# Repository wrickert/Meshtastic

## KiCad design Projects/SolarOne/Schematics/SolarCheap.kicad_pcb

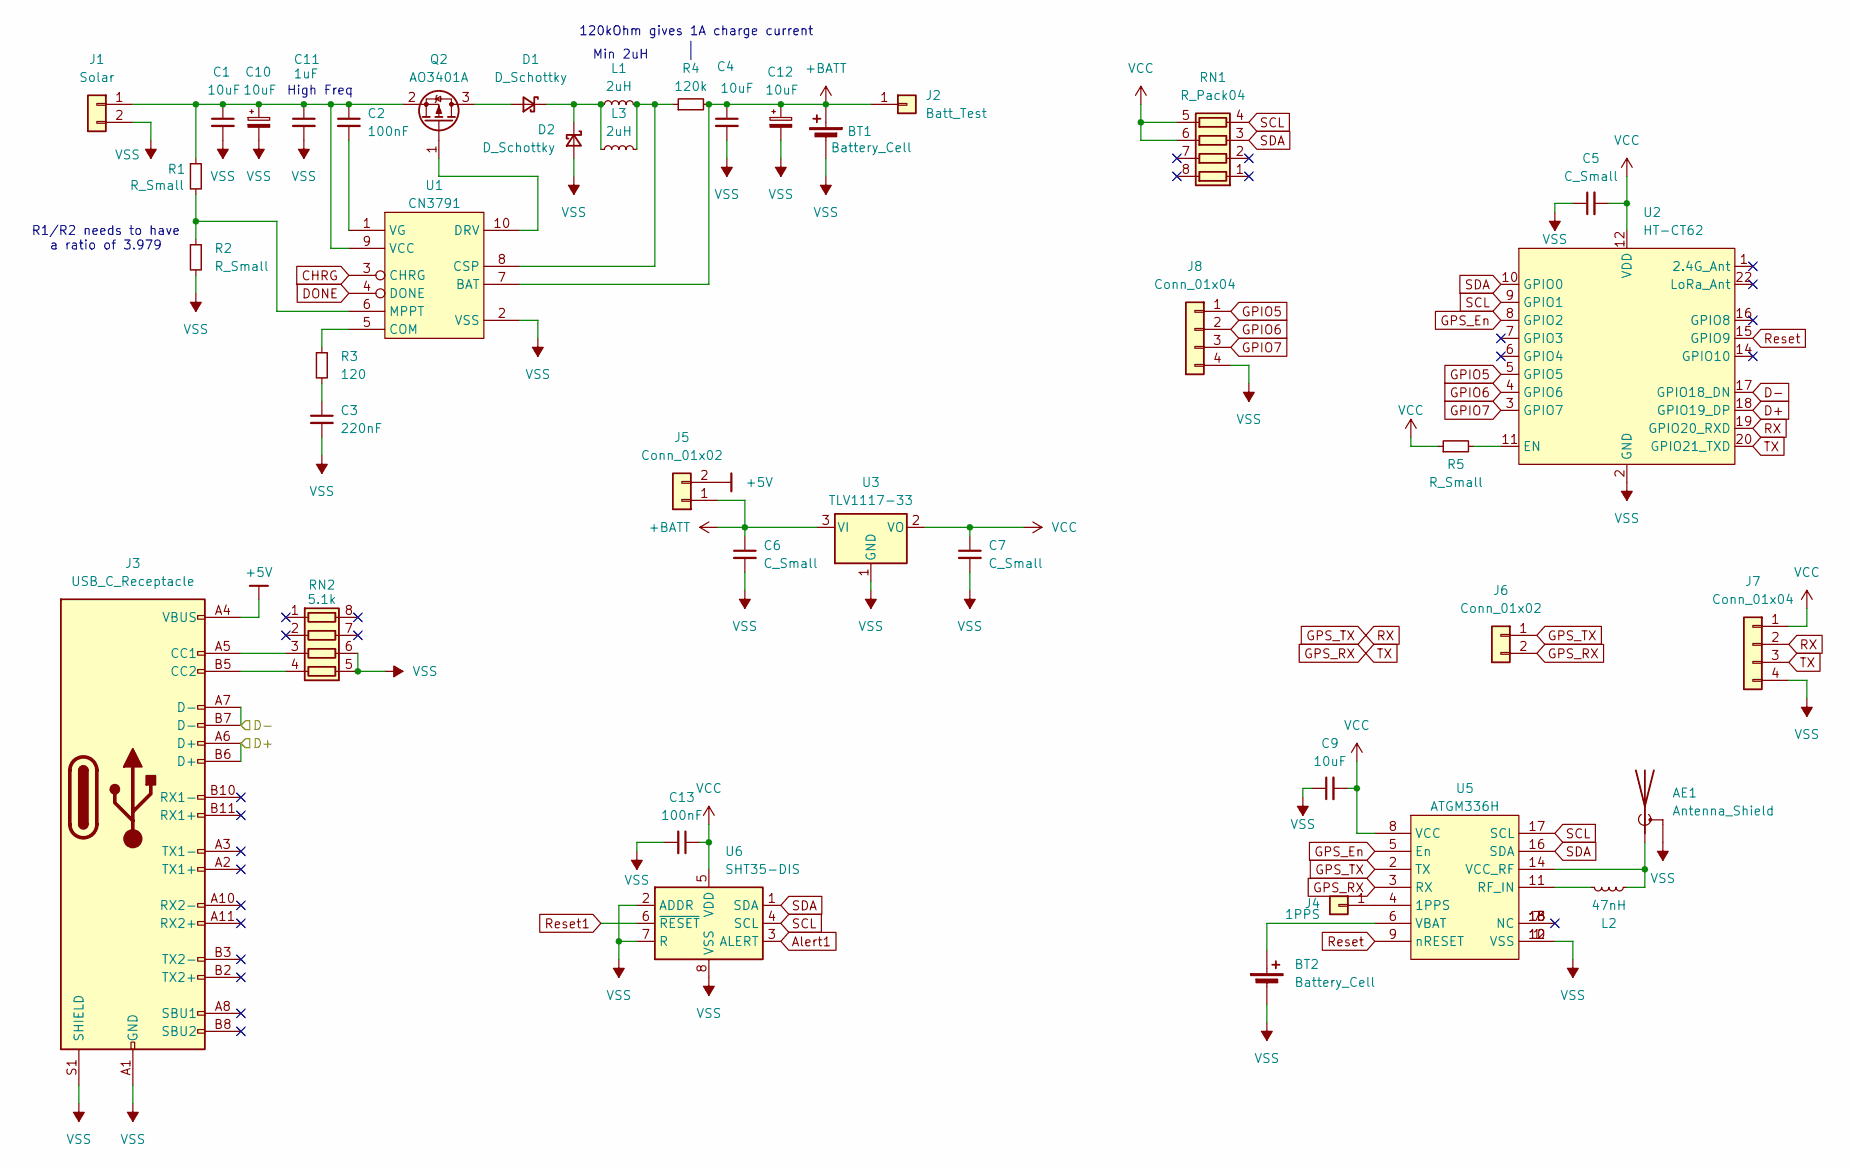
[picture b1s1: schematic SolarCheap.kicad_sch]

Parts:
AE1: Antenna_Shield; U.FL_Molex_MCRF_73412-0110_Vertical
BT1: Battery_Cell; BatteryHolder_Keystone_1042_1x18650
BT2: Battery_Cell; SEIKO_ML414H_IV01E
C1, C4, C9: 10uF; C_0805_2012Metric
C2, C13: 100nF; C_0805_2012Metric
C3: 220nF; C_0805_2012Metric
C5, C6, C7: C_Small; C_0805_2012Metric
C10, C12: 10uF; CP_Elec_4x5.4
C11: 1uF; C_0805_2012Metric
D1, D2: D_Schottky; D_0805_2012Metric
J1: Solar; PhoenixContact_MSTBA_2,5_2-G-5,08_1x02_P5.08mm_Horizontal
J2: Batt_Test; PinHeader_1x01_P2.54mm_Vertical
J3: USB_C_Receptacle; USB_C_Receptical-Jing
J4: 1PPS; PinHeader_1x01_P2.54mm_Vertical
J5, J6: Conn_01x02; PinHeader_1x02_P2.54mm_Vertical
J7: Conn_01x04; PinHeader_1x04_P2.54mm_Vertical
J8: Conn_01x04; PinHeader_1x04_P1.27mm_Vertical
L1: 2uH; L_7.3x7.3_H3.5
L2: 47nH; L_0805_2012Metric
L3: 2uH; L_1008_2520Metric
Q2: AO3401A; SOT-23
R1, R2, R5: R_Small; R_0805_2012Metric
R3: 120; R_0805_2012Metric
R4: 120k; R_0805_2012Metric
RN1: R_Pack04; R_Array_Convex_4x0603
RN2: 5.1k; R_Array_Concave_4x0603
U1: CN3791; SSOP-10_3.9x4.9mm_P1.00mm
U2: HT-CT62; Heltec_HT-CT62
U3: TLV1117-33; SOT-223-3_TabPin2
U5: ATGM336H
U6: SHT35-DIS; Sensirion_DFN-8-1EP_2.5x2.5mm_P0.5mm_EP1.1x1.7mm

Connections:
+5V: J3.A4 (VBUS), J3.A9 (VBUS), J3.B4 (VBUS), J3.B9 (VBUS), J5.2
+BATT: BT1.1 (+), C4.1, C6.1, C12.1, J2.1, J5.1, R4.2, U1.7 (BAT), U3.3 (VI)
CHRG: U1.3 (CHRG)
D+: J3.A6 (D+), J3.B6 (D+), U2.18 (GPIO19_DP)
D-: J3.A7 (D-), J3.B7 (D-), U2.17 (GPIO18_DN)
DONE: U1.4 (DONE)
GPIO5: J8.1, U2.5 (GPIO5)
GPIO6: J8.2, U2.4 (GPIO6)
GPIO7: J8.3, U2.3 (GPIO7)
GPS_En: U2.8 (GPIO2), U5.5 (En)
GPS_RX: J6.2, J7.3, U2.20 (GPIO21_TXD), U5.3 (RX)
GPS_TX: J6.1, J7.2, U2.19 (GPIO20_RXD), U5.2 (TX)
unnamed: AE1.1 (A), L2.2, U5.14 (VCC_RF)
unnamed: BT2.1 (+), U5.6 (VBAT)
unnamed: C3.1, R3.2
unnamed: D1.2 (A), Q2.3 (D)
unnamed: D1.1 (K), D2.1 (K), L1.1, L3.1
unnamed: C1.1, C2.1, C10.1, C11.1, J1.1, Q2.2 (S), R1.1, U1.9 (VCC)
unnamed: J3.A5 (CC1), RN2.3 (R3.1)
unnamed: J3.B5 (CC2), RN2.4 (R4.1)
unnamed: J4.1, U5.4 (1PPS)
unnamed: Q2.1 (G), U1.10 (DRV)
unnamed: R3.1, U1.5 (COM)
unnamed: L1.2, L3.2, R4.1, U1.8 (CSP)
unnamed: R1.2, R2.1, U1.6 (MPPT)
unnamed: C2.2, U1.1 (VG)
unnamed: R5.2, U2.11 (EN)
unnamed: L2.1, U5.11 (RF_IN)
Reset: U2.15 (GPIO9), U5.9 (nRESET)
SCL: RN1.4 (R4.1), U2.9 (GPIO1), U5.17 (SCL), U6.4 (SCL); also elsewhere on the board
SDA: RN1.3 (R3.1), U2.10 (GPIO0), U5.16 (SDA), U6.1 (SDA); also elsewhere on the board
VCC: C5.2, C7.1, C9.2, C13.1, J7.1, R5.1, RN1.5 (R4.2), RN1.6 (R3.2), U2.12 (VDD), U3.2 (VO), U5.8 (VCC), U6.5 (VDD); also elsewhere on the board
VSS: AE1.2 (Shield), BT1.2 (-), BT2.2 (-), C1.2, C3.2, C4.2, C5.1, C6.2, C7.2, C9.1, C10.2, C11.2, C12.2, C13.2, D2.2 (A), J1.2, J3.A1 (GND), J3.A12 (GND), J3.B1 (GND), J3.B12 (GND), J3.S1 (SHIELD), J7.4, J8.4, R2.2, RN2.5 (R4.2), RN2.6 (R3.2), U1.2 (VSS), U2.2 (GND), U2.13 (GND), U2.21 (GND), U3.1 (GND), U5.1 (VSS), U5.10 (VSS), U5.12 (VSS), U6.2 (ADDR), U6.7 (R), U6.8 (VSS), U6.9 (VSS); also elsewhere on the board

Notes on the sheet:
R1/R2 needs to have a ratio of 3.979
Min 2uH
120kOhm gives 1A charge current
High Freq

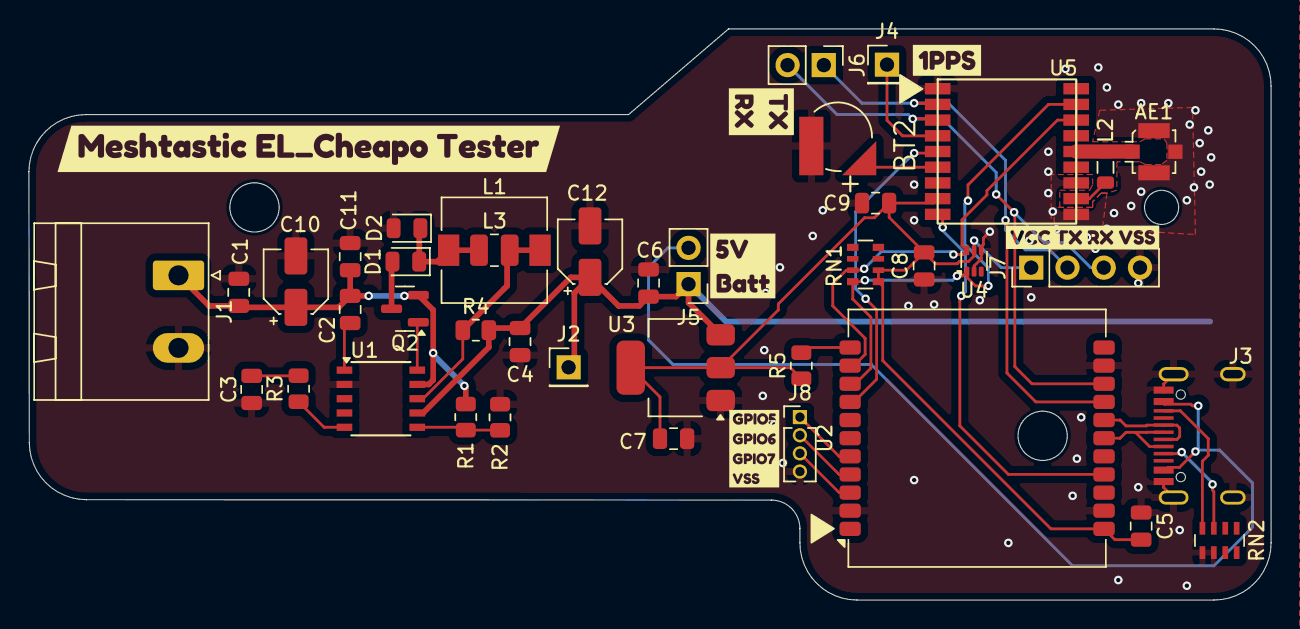
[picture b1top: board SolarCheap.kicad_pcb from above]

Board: 2 copper layers, 87.0 x 40.0 mm, 47 parts (1 on the bottom side), 31 nets.

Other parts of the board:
C8: 100nF; C_0805_2012Metric
U4: TMP102xxDRL; SOT-563
kibuzzard-66621C54: G***; kibuzzard-66621C54
kibuzzard-66621C64: G***; kibuzzard-66621C64
kibuzzard-66621C74: G***; kibuzzard-66621C74
kibuzzard-666316A7: G***; kibuzzard-666316A7
kibuzzard-6663166B: G***; kibuzzard-6663166B
kibuzzard-66621754: G***; kibuzzard-66621754

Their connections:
SCL: U4.1 (SCL); also elsewhere on the board
SDA: U4.6 (SDA); also elsewhere on the board
VCC: C8.2, U4.5 (V+); also elsewhere on the board
VSS: C8.1, U4.2 (GND), U4.4 (ADD0); also elsewhere on the board

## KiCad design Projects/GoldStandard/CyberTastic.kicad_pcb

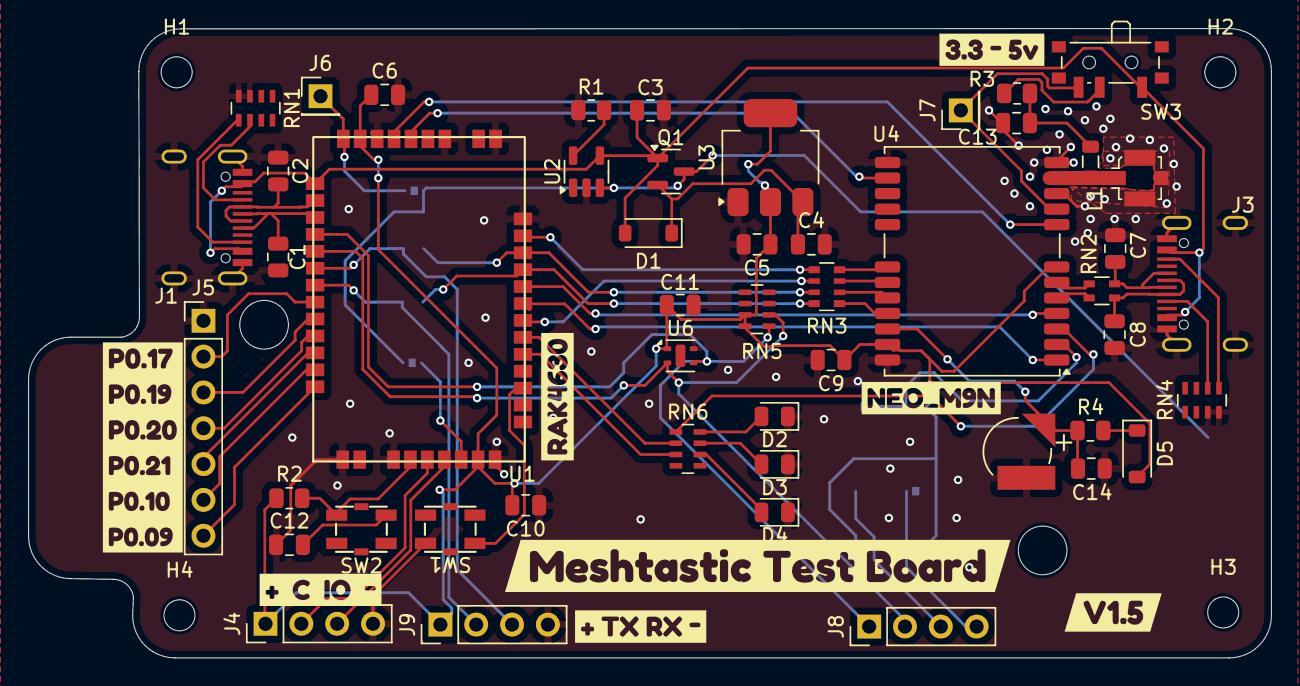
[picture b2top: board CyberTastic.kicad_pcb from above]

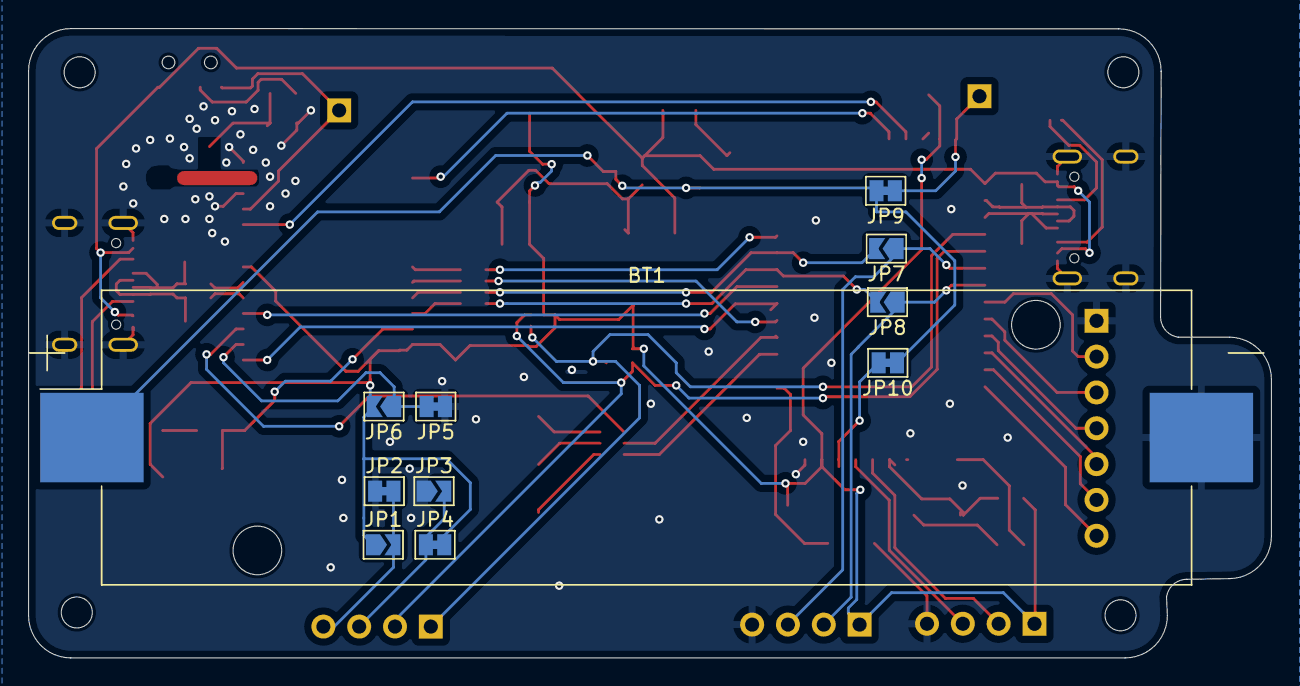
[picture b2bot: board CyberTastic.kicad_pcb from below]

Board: 2 copper layers, 88.1 x 44.6 mm, 72 parts (11 on the bottom side), 60 nets.

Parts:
BT1: Battery_Cell; BatteryHolder_Keystone_1042_1x18650
BT2: Battery_Cell; SEIKO_ML414H_IV01E
C1, C2, C7, C8: TBD; C_0805_2012Metric
C3: 22uF; C_0805_2012Metric
C4, C5: 10uF; C_0805_2012Metric
C6, C9, C10, C11, C12, C13, C14: 100nF; C_0805_2012Metric
D1, D5: D_Schottky; D_SOD-123
D2, D3, D4: LED_Small; LED_0805_2012Metric
H1, H2, H3, H4: MountingHole; MountingHole_2.2mm_M2
J1, J3: USB_C_Receptacle; USB_C_Receptical-Jing
J2: U.FL; U.FL_Molex_MCRF_73412-0110_Vertical
J4, J9: Conn_01x04; PinHeader_1x04_P2.54mm_Vertical
J5: Conn_01x07; PinHeader_1x07_P2.54mm_Vertical
J6: Bodge; PinHeader_1x01_P2.54mm_Vertical
J7: Conn_01x01; PinHeader_1x01_P2.54mm_Vertical
J8: OledDisplay; PinHeader_1x04_P2.54mm_Vertical
JP1: JOpen; SolderJumper-2_P1.3mm_Open_TrianglePad1.0x1.5mm
JP2: JClosed; SolderJumper-2_P1.3mm_Bridged_Pad1.0x1.5mm
JP3, JP6, JP7, JP8: Jumper_2_Open; SolderJumper-2_P1.3mm_Open_TrianglePad1.0x1.5mm
JP4, JP5, JP9, JP10: Jumper_2_Bridged; SolderJumper-2_P1.3mm_Bridged_Pad1.0x1.5mm
L1: 27nH; L_0805_2012Metric
Q1: AO3401A; SOT-23
R1: R_Small; R_0805_2012Metric
R2: 10k; R_0805_2012Metric
R3: 10; R_0805_2012Metric
R4: 1k; R_0805_2012Metric
RN1, RN4, RN5, RN6: 5.1k; R_Array_Concave_4x0603
RN2: 27; R_Array_Convex_2x0603
RN3: 33; R_Array_Convex_4x0603
SW1, SW2: SW_SPST; TS3315A
SW3: SW_SPDT; SW_SPDT_PCM12
U1: RAK4630
U2: LTC4054ES5; TSOT-23-5
U3: TLV1117-33; SOT-223-3_TabPin2
U4: NEO-M9N; ublox_NEO
U6: SHTC3; Sensirion_DFN-4-1EP_2x2mm_P1mm_EP0.7x1.6mm
kibuzzard-665A1BDF: G***; kibuzzard-665A1BDF
kibuzzard-665A1C19: G***; kibuzzard-665A1C19
kibuzzard-665A1C85: G***; kibuzzard-665A1C85
kibuzzard-665A1CA2: G***; kibuzzard-665A1CA2
kibuzzard-665A1CD2: G***; kibuzzard-665A1CD2
kibuzzard-665A1D5A: G***; kibuzzard-665A1D5A
kibuzzard-665A1D6B: G***; kibuzzard-665A1D6B
kibuzzard-667C6B2E: G***; kibuzzard-667C6B2E

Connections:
+5V: C3.2, D1.2 (A), J1.A4 (VBUS), J1.A9 (VBUS), J1.B4 (VBUS), J1.B9 (VBUS), J3.A4 (VBUS), J3.A9 (VBUS), J3.B4 (VBUS), J3.B9 (VBUS), Q1.1 (G), SW3.1 (A), U1.1 (VBus), U2.4 (V_{CC})
/D+: C1.1, J1.A6 (D+), J1.B6 (D+), U1.3 (D+)
/D-: C2.1, J1.A7 (D-), J1.B7 (D-), U1.2 (D-)
/RX/MOSI: JP8.2 (B), RN3.8 (R1.2), U1.32 (P0.29)
/SCL/CLK: RN3.6 (R3.2), U1.29 (P0.03)
/SDA/CS: RN3.5 (R4.2), U1.34 (P0.26)
/TX/MISO: JP7.2 (B), RN3.7 (R2.2), U1.33 (P0.30)
Batt: BT1.1 (+), JP9.2 (B), JP10.1 (A), Q1.3 (D), U2.3 (BAT)
Data_Sel: JP5.2 (B), JP6.1 (A), U4.2 (D_SEL)
EXTINT: U1.31 (P0.28), U4.4 (EXTINT)
GPS_D+: C7.1, J3.A6 (D+), J3.B6 (D+), RN2.4 (R1.2)
GPS_D-: C8.1, J3.A7 (D-), J3.B7 (D-), RN2.3 (R2.2)
LED1: RN6.3 (R3.1), U1.27 (P1.03)
LED2: RN6.2 (R2.1), U1.28 (P1.04)
LND_EN: U1.40 (P0.05), U4.14 (LNA_EN)
unnamed: BT2.1 (+), C14.1, R4.1, U4.22 (V_BCKP)
unnamed: C13.1, L1.2, R3.1
unnamed: C4.1, D1.1 (K), Q1.2 (S), U3.3 (VI)
unnamed: D2.2 (A), RN6.8 (R1.2)
unnamed: D3.2 (A), RN6.7 (R2.2)
unnamed: D4.2 (A), RN6.6 (R3.2)
unnamed: D5.1 (K), R4.2
unnamed: J1.A5 (CC1), RN1.6 (R3.2)
unnamed: J1.B5 (CC2), RN1.5 (R4.2)
unnamed: J2.1 (In), L1.1, U4.11 (RF_IN)
unnamed: J3.A5 (CC1), RN4.6 (R3.2)
unnamed: J3.B5 (CC2), RN4.5 (R4.2)
unnamed: J6.1, JP9.1 (A), U1.44 (VBAT_NRF)
unnamed: J7.1, SW3.3 (C), U4.9 (VCC_RF)
unnamed: J8.3, JP3.2 (B), JP4.1 (A)
unnamed: J8.4, JP1.2 (B), JP2.2 (B)
unnamed: JP10.2 (B), U1.20 (VBatt_SX)
unnamed: RN2.1 (R1.1), U4.6 (USB_DP)
unnamed: RN2.2 (R2.1), U4.5 (USB_DM)
unnamed: RN3.1 (R1.1), U4.21 (RXD/SPI_MOSI)
unnamed: RN3.2 (R2.1), U4.20 (TXD/SPI_MISO)
unnamed: RN3.3 (R3.1), U4.19 (SCL/SPI_CLK)
unnamed: RN3.4 (R4.1), U4.18 (SDA/~SPI_CS)
unnamed: SW1.1 (A), U1.25 (P1.01)
unnamed: R2.1, SW2.1 (A), U1.17 (Reset)
unnamed: C12.2, SW2.2 (B)
unnamed: R3.2, SW3.2 (B)
unnamed: R1.2, U2.5 (PROG)
P0.09: J5.7, U1.13 (P0.09)
P0.10: J5.6, U1.12 (P0.10)
P0.17: J5.2, U1.8 (P0.17)
P0.19: J5.3, U1.9 (P0.19)
P0.20: J5.4, U1.10 (P0.20)
P0.21: J5.5, U1.11 (P0.21)
RESET: U1.41 (P0.04), U4.8 (~RESET)
RX: J9.3, JP7.1 (A), U1.6 (P0.15)
SAFEBOOT: U1.30 (P0.02), U4.1 (~SAFEBOOT)
SCL: J8.2, RN5.6 (R3.2), U1.5 (P0.14), U6.2 (SCL)
SDA: J8.1, RN5.5 (R4.2), U1.4 (P0.13), U6.3 (SDA)
SWDCLK: J4.2, U1.18 (SWDCLK)
SWDIO: J4.3, U1.19 (SWDIO)
TX: J9.2, JP8.1 (A), U1.7 (P0.16)
Timepulse: RN6.1 (R1.1), U4.3 (TIMEPULSE)
VCC: C5.1, C6.1, C9.1, C10.2, C11.2, D5.2 (A), J4.1, J9.1, JP1.1 (A), JP4.2 (B), JP6.2 (B), R2.2, RN5.3 (R3.1), RN5.4 (R4.1), U1.21 (VBAT_IO_SX), U1.43 (VDD_NRF), U3.2 (VO), U4.7 (VDD_USB), U4.23 (VCC), U6.1 (VDD)
VSS: BT1.2 (-), BT2.2 (-), C1.2, C2.2, C3.1, C4.2, C5.2, C6.2, C7.2, C8.2, C9.2, C10.1, C11.1, C12.1, C13.2, C14.2, D2.1 (K), D3.1 (K), D4.1 (K), J1.A1 (GND), J1.A12 (GND), J1.B1 (GND), J1.B12 (GND), J1.S1 (SHIELD), J2.2 (Ext), J3.A1 (GND), J3.A12 (GND), J3.B1 (GND), J3.B12 (GND), J3.S1 (SHIELD), J4.4, J5.1, J9.4, JP2.1 (A), JP3.1 (A), JP5.1 (A), R1.1, RN1.3 (R3.1), RN1.4 (R4.1), RN4.3 (R3.1), RN4.4 (R4.1), SW1.2 (B), U1.14 (VSS), U1.16 (VSS), U1.22 (VSS), U1.35 (VSS), U1.36 (VSS), U1.38 (VSS), U1.42 (VSS), U2.2 (GND), U3.1 (GND), U4.10 (GND), U4.12 (GND), U4.13 (GND), U4.24 (GND), U6.4 (VSS)

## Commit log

2024-06-20 Added pdf schematics
2025-01-06 Fixed SolarOne and other
